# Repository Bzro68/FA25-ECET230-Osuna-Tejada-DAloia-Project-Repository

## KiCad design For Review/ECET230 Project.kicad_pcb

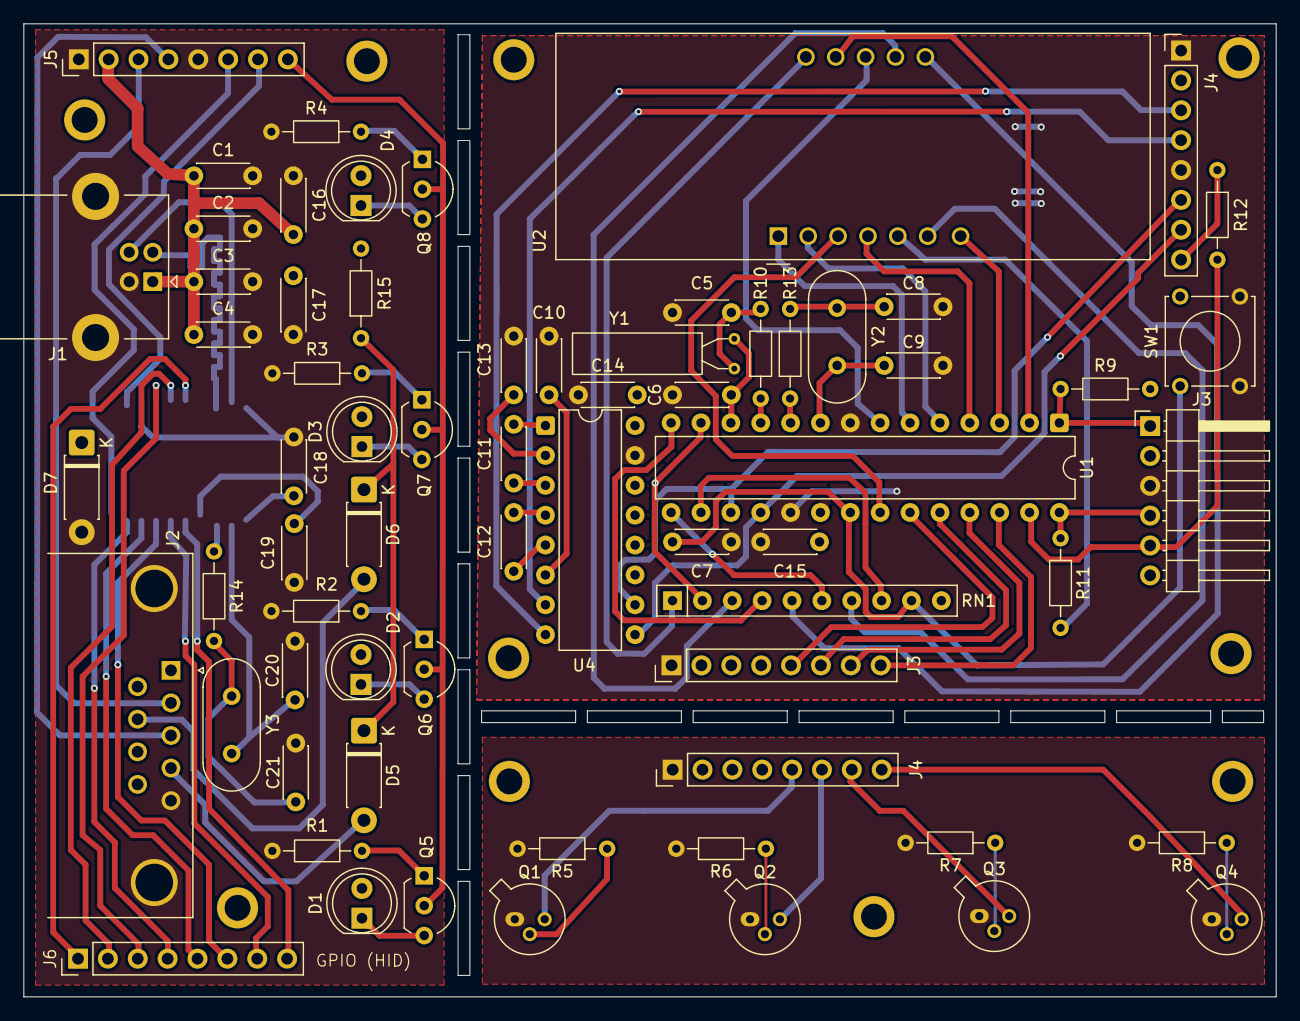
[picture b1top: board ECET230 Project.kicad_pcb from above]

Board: 2 copper layers, 106.5 x 82.8 mm, 78 parts (1 on the bottom side), 46 nets, no tracks yet.

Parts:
C1, C16, C17: 10uF; C_Disc_D4.3mm_W1.9mm_P5.00mm
C2, C10, C11, C12, C13: 1uF; C_Disc_D4.3mm_W1.9mm_P5.00mm
C3, C14, C15, C18, C19: 100nF; C_Disc_D4.3mm_W1.9mm_P5.00mm
C4, C7: 10nF; C_Disc_D4.3mm_W1.9mm_P5.00mm
C5, C6: 100pF; C_Disc_D4.3mm_W1.9mm_P5.00mm
C8, C9: 33pF; C_Disc_D4.3mm_W1.9mm_P5.00mm
C20, C21: 20pF; C_Disc_D4.3mm_W1.9mm_P5.00mm
D1, D2, D3, D4: LED56; LED_D5.0mm_IRGrey
D5, D6: 1N5817; D_DO-41_SOD81_P7.62mm_Horizontal
D7: 1N4733A; D_DO-41_SOD81_P7.62mm_Horizontal
H1, H2, H3, H4, H5, H6, H7, H8, H9, H10: MountingHole_2.2mm_M2_ISO7380_Pad
J1: USB_B; USB_B_Lumberg_2411_02_Horizontal
J2: Female DE9; DSUB-9_Pins_Horizontal_P2.77x2.84mm_EdgePinOffset7.70mm_Hou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
J3, J4, J4#2, J5, J6: PinHeader_1x08_P2.54mm_Vertical
J3#2: 01x06; PinHeader_1x06_P2.54mm_Horizontal
Q1, Q2, Q3, Q4: L14P2; TO-18-3_Lens
Q5, Q6, Q7, Q8: 2N3904; TO-92L_Inline_Wide
R1, R2, R3, R4, R11, R12: 100; R_Axial_DIN0204_L3.6mm_D1.6mm_P7.62mm_Horizontal
R5, R6, R7, R8: 1M; R_Axial_DIN0204_L3.6mm_D1.6mm_P7.62mm_Horizontal
R9: 10K; R_Axial_DIN0204_L3.6mm_D1.6mm_P7.62mm_Horizontal
R10: 47K; R_Axial_DIN0204_L3.6mm_D1.6mm_P7.62mm_Horizontal
R13: 430; R_Axial_DIN0204_L3.6mm_D1.6mm_P7.62mm_Horizontal
R14: 680; R_Axial_DIN0204_L3.6mm_D1.6mm_P7.62mm_Horizontal
R15: 820; R_Axial_DIN0204_L3.6mm_D1.6mm_P7.62mm_Horizontal
RN1: 1K; R_Array_SIP10
SW1: SW_SPST; SW_Tactile_Straight_KSA0Axx1LFTR
U1: PIC16F883-IP; DIP-28_W7.62mm
U2: HDSP-B03E; CA56-12EWA
U3: MCP2200; SOIC-20W_7.5x12.8mm_P1.27mm
U4: MAX232; DIP-16_W7.62mm
Y1: 32.768KHz; Crystal_AT310_D3.0mm_L10.0mm_Horizontal
Y2: 11.0592MHz; Crystal_HC49-4H_Vertical
Y3: 12MHz; Crystal_HC49-4H_Vertical

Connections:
7-G: R11.2, U2.5 (g)
CC1: RN1.2 (R1.2), U1.13 (RC2/P1A/CCP1)
CC2: RN1.4 (R2.2), U1.14 (RC3/SCK/SCL)
CC3: RN1.6 (R3.2), U1.15 (RC4/SDI/SDA)
CC4: RN1.8 (R4.2), U1.16 (RC5/SDO)
DP: U1.22 (P1C/AN10/RB1), U2.3 (DPX)
GNDREF: C1.2, C2.2, C3.2, C4.2, C5.2, C6.2, C7.2, C8.2, C9.2, C10.1, C13.1, C14.2, C15.2, C16.1, C17.2, C18.1, C19.2, C20.1, C21.1, D7.2, J1.4 (GND), J1.5 (Shield), J2.0 (PAD), J2.5, J3.1, J3#2.3, J4.1, J4#2.1, J4#2.5, J5.1, J5.5, Q1.1 (E), Q2.1 (E), Q3.1 (E), Q4.1 (E), R1.2, R2.2, R3.2, R4.2, R5.2, R6.2, R7.2, R8.2, SW1.2 (B), U1.8 (VSS), U1.19 (VSS), U4.15 (GND)
ICSPCLK: J3#2.5, R12.1, U1.27 (ICSPCLK/RB6)
ICSPDAT: J3#2.4, R11.1, U1.28 (ICSPDAT/RB7)
unnamed: C5.1, R10.2, Y1.2
unnamed: C8.1, R13.2, Y2.2
unnamed: Q1.2 (B), R5.1
unnamed: Q2.2 (B), R6.1
unnamed: Q3.2 (B), R7.1
unnamed: Q4.2 (B), R8.1
unnamed: RN1.1 (R1.1), U2.12 (CC1)
unnamed: RN1.3 (R2.1), U2.9 (CC2)
unnamed: RN1.5 (R3.1), U2.8 (CC3)
unnamed: RN1.7 (R4.1), U2.6 (CC4)
unnamed: U1.5 (C1IN+/Vref+/AN3/RA3), U2.2 (d)
unnamed: U1.3 (C12IN1-/AN1/RA1), U2.7 (b)
unnamed: C9.1, U1.9 (CLKIN/OSC1/RA7), Y2.1
unnamed: R13.1, U1.10 (CLKOUT/OSC2/RA6)
unnamed: U1.4 (CVref/C2IN1+/Vref-/AN2/RA2), U2.4 (c)
unnamed: R10.1, U1.11 (RC0/T1OSO/T1CK1)
unnamed: C6.1, U1.12 (RC1/T1OSI/CCP2), Y1.1
unnamed: U1.6 (T0CKI/C1OUT/RA4), U2.1 (e)
unnamed: U1.2 (ULPWU/C12IN0-/AN0/RA0), U2.11 (a)
unnamed: U1.7 (~SS/C2OUT/AN4/RA5), U2.10 (f)
unnamed: C11.1, U4.1 (C1+)
unnamed: C11.2, U4.3 (C1-)
unnamed: C12.1, U4.4 (C2+)
unnamed: C12.2, U4.5 (C2-)
unnamed: J2.2, J4#2.3, J5.3, U4.8 (R2IN)
unnamed: J2.3, J4#2.4, J5.4, U4.7 (T2OUT)
OUT1: Q1.3 (C), U1.23 (P1B/AN8/RB2)
OUT2: Q2.3 (C), U1.24 (PGM/C12IN2-/AN8/RB3)
OUT3: Q3.3 (C), U1.25 (P1D/AN11/RB4)
OUT4: Q4.3 (C), U1.26 (~T1G/AN13/RB5)
RB0: C7.1, RN1.9 (R5.1), SW1.1 (A), U1.21 (INT/AN12/RB0)
RX: U1.18 (RC7/RX/DT), U4.9 (R2OUT)
TX: U1.17 (RC6/TX/CK), U4.10 (T2IN)
V+: C13.2, U4.2 (VS+)
V-: C10.2, U4.6 (VS-)
VDD: C1.1, C2.1, C3.1, C4.1, C14.1, C15.1, C16.2, C17.1, C18.2, D1.2 (A), D2.2 (A), D3.2 (A), D4.2 (A), D7.1, J1.1 (VBUS), J3.2, J3#2.2, J4.2, J4#2.2, J5.2, R9.1, R15.2, RN1.10 (R5.2), U1.20 (VDD), U4.16 (VCC)
~MCLR/VPP: J3#2.1, R9.2, U1.1 (RE3/~MCLR/Vpp)

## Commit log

2025-09-18 Create New File
2025-09-18 Rename ECET_230_Project_Definition - 9_17_25 (1).docx to Documentation/ECET_230_Project_Definition - 9_17_25 (1).docx
2025-09-18 Rename FA25-ECET230 - Design Decisions - Coin Counter - 9_17_25.docx to Documentation/FA25-ECET230 - Design Decisions - Coin Counter - 9_17_25.docx
2025-09-18 Rename FA25-ECET230 - Logbook - Coin Counter - 9_17_25.docx to Documentation/FA25-ECET230 - Logbook - Coin Counter - 9_17_25.docx
2025-09-21 FA25-ECET230-Osuna-Tejada-DAloia-Project-Repository/For Review/
2025-09-21 Rename Circuit description.md to Circuit_DRAFT_description.md
2025-09-23 Updated with current components
2025-09-23 Delete Documentation/FA25-ECET230 - Design Decisions - Coin Counter - 9_17_25.pdf
    Will replace with newer version
2025-09-23 Add files via upload
    Newer version of Design Decision doc (9/22/25)
2025-10-03 About
